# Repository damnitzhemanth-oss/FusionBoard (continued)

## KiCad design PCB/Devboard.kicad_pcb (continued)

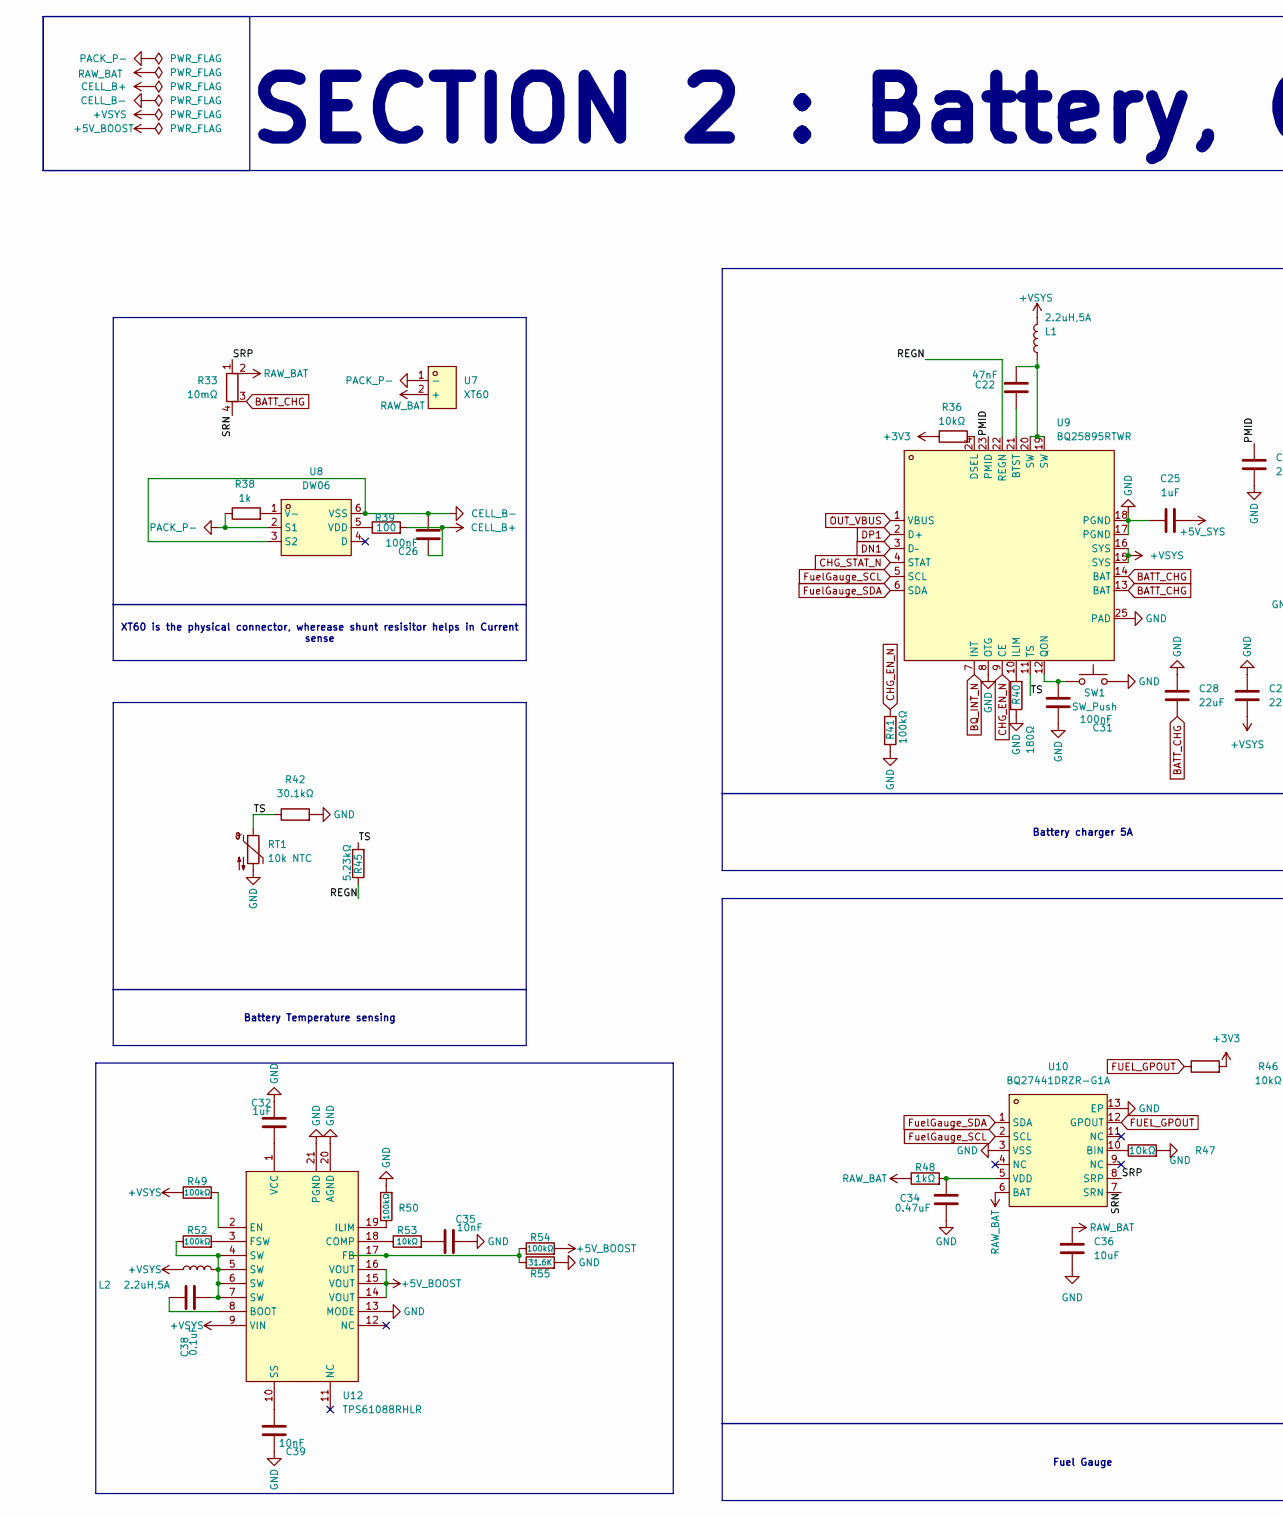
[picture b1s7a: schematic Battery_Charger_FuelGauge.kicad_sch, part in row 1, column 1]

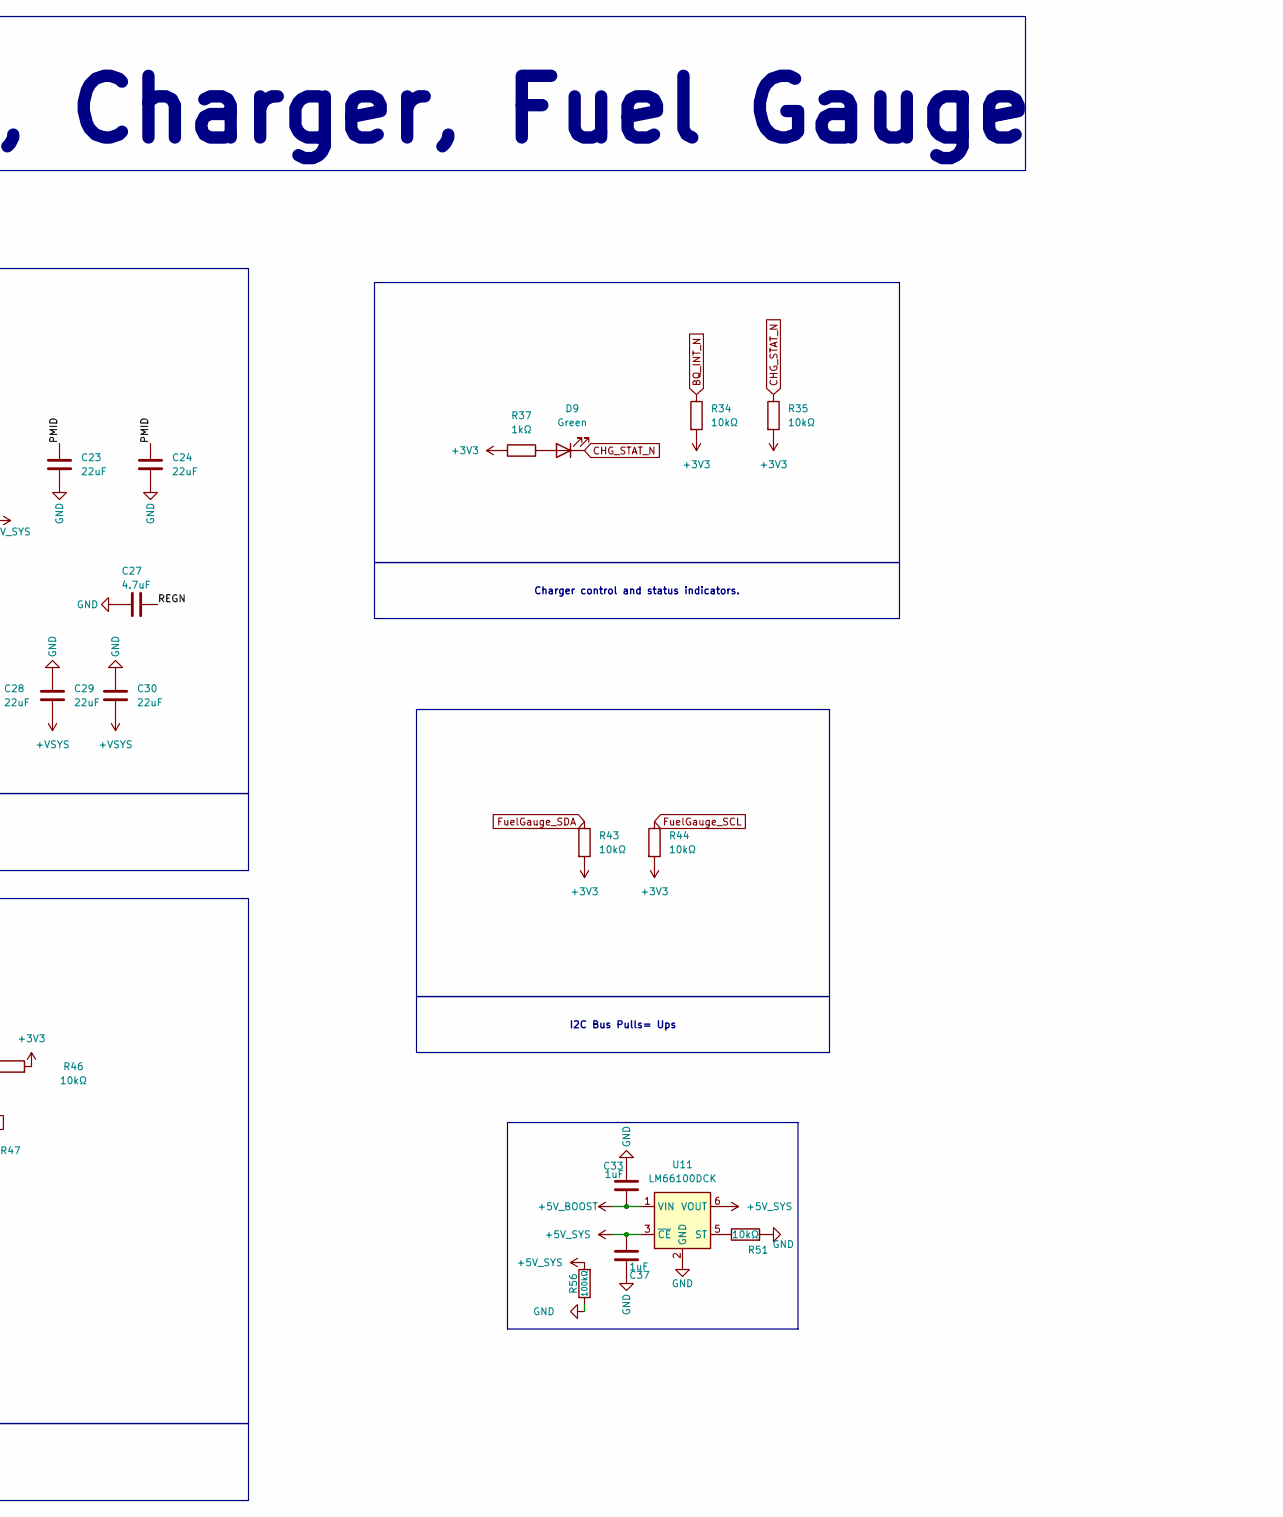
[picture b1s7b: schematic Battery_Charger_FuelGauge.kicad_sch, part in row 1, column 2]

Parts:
C22: 47nF; C_0402_1005Metric
C23, C24, C28, C29, C30: 22uF; C_0805_2012Metric
C25: 1uF; C_0402_1005Metric
C26, C31: 100nF; C_0402_1005Metric
C27: 4.7uF; C_0603_1608Metric
C32, C33, C37: 1uF; C_0805_2012Metric
C34: 0.47uF; C_0402_1005Metric
C35, C39: 10nF; C_0805_2012Metric
C36: 10uF; C_0402_1005Metric
C38: 0.1uF; C_0805_2012Metric
D9: Green; LED_0603_1608Metric
L1, L2: 2.2uH,5A; L_Bourns_SRP1245A
R33: 10mΩ; R_Shunt_Isabellenhuette_BVR4026
R34, R35, R36, R43, R44, R46, R47, R51, R53: 10kΩ; R_0402_1005Metric
R37, R48: 1kΩ; R_0402_1005Metric
R38: 1k; R_0402_1005Metric
R39: 100; R_0402_1005Metric
R40: 180Ω; R_0402_1005Metric
R41, R49, R50, R52, R54, R56: 100kΩ; R_0402_1005Metric
R42: 30.1kΩ; R_0402_1005Metric
R45: 5.23kΩ; R_0402_1005Metric
R55: 31.6K; R_0402_1005Metric
RT1: 10k NTC; R_0603_1608Metric
SW1: SW_Push; SW_SPST_Omron_B3FS-100xP
U7: XT60; CONN-TH_XT60; MPN XT60-M.; LCSC Part C98733
U8: DW06; SOT-23-6_L2.9-W1.6-P0.95-LS2.8-BL; MPN DW06; LCSC Part C917080
U9: BQ25895RTWR; QFN-24_L4.0-W4.0-P0.50-TL-EP2.7; MPN BQ25895RTWR; LCSC Part C80200
U10: BQ27441DRZR-G1A; SON-12_L4.0-W2.5-P0.40-BL-EP; MPN BQ27441DRZR-G1A; LCSC Part C473397
U11: LM66100DCK; SOT-363_SC-70-6
U12: TPS61088RHLR; VQFN-20_L4.6-W3.6-P0.50-BL; MPN TPS61088RHLR; LCSC Part C87357

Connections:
+3V3: R34.2, R35.2, R36.1, R37.1, R43.2, R44.2, R46.2; also elsewhere on the board
+5V_BOOST: C33.2, R54.2, U11.1 (VIN), U12.14 (VOUT), U12.15 (VOUT), U12.16 (VOUT)
+5V_SYS: C25.2, C37.2, R56.2, U11.3 (~CE), U11.6 (VOUT); also elsewhere on the board
+VSYS: C29.1, C30.1, L1.2, L2.1, R49.1, U9.15 (SYS), U9.16 (SYS), U12.9 (VIN)
/Battery.Charger,Fuel Gauge/PMID: C23.2, C24.2, U9.23 (PMID)
/Battery.Charger,Fuel Gauge/REGN: C27.1, R45.1, U9.22 (REGN)
/Battery.Charger,Fuel Gauge/SRN: R33.4, U10.7 (SRN)
/Battery.Charger,Fuel Gauge/SRP: R33.1, U10.8 (SRP)
/Battery.Charger,Fuel Gauge/TS: R42.1, R45.2, RT1.1, U9.11 (TS)
BATT_CHG: C28.1, R33.3, U9.13 (BAT), U9.14 (BAT)
BQ_INT_N: R34.1, U9.7 (INT)
CELL_B+: C26.1, R39.2
CELL_B-: C26.2, U8.3 (S2), U8.6 (VSS)
CHG_EN_N: R41.2, U9.9 (CE)
CHG_STAT_N: D9.1 (K), R35.1, U9.4 (STAT)
DN1: U9.3 (D–); also elsewhere on the board
DP1: U9.2 (D+); also elsewhere on the board
FUEL_GPOUT: R46.1, U10.12 (GPOUT)
FuelGauge_SCL: R44.1, U9.5 (SCL), U10.2 (SCL)
FuelGauge_SDA: R43.1, U9.6 (SDA), U10.1 (SDA)
GND: C23.1, C24.1, C25.1, C27.2, C28.2, C29.2, C30.2, C31.1, C32.1, C33.1, C34.1, C35.1, C36.1, C37.1, C39.1, R40.1, R41.1, R42.2, R47.2, R50.2, R51.2, R55.2, R56.1, RT1.2, SW1.2, U9.8 (OTG), U9.17 (PGND), U9.18 (PGND), U9.25 (PAD), U10.3 (VSS), U10.13 (EP), U11.2 (GND), U12.13 (MODE), U12.20 (AGND), U12.21 (PGND); also elsewhere on the board
unnamed: C22.2, L1.1, U9.19 (SW), U9.20 (SW)
unnamed: C35.2, R53.2
unnamed: C38.1, L2.2, R52.1, U12.4 (SW), U12.5 (SW), U12.6 (SW), U12.7 (SW)
unnamed: D9.2 (A), R37.2
unnamed: R38.2, U8.1 (V-)
unnamed: R39.1, U8.5 (VDD)
unnamed: C22.1, U9.21 (BTST)
unnamed: R36.2, U9.24 (DSEL)
unnamed: R40.2, U9.10 (ILIM)
unnamed: C31.2, SW1.1, U9.12 (QON)
unnamed: R47.1, U10.10 (BIN)
unnamed: C34.2, R48.2, U10.5 (VDD)
unnamed: R51.1, U11.5 (ST)
unnamed: C38.2, U12.8 (BOOT)
unnamed: R53.1, U12.18 (COMP)
unnamed: R49.2, U12.2 (EN)
unnamed: R54.1, R55.1, U12.17 (FB)
unnamed: R52.2, U12.3 (FSW)
unnamed: R50.1, U12.19 (ILIM)
unnamed: C39.2, U12.10 (SS)
unnamed: C32.2, U12.1 (VCC)
OUT_VBUS: U9.1 (VBUS); also elsewhere on the board
PACK_P-: R38.1, U7.1 (-), U8.2 (S1)
RAW_BAT: C36.2, R33.2, R48.1, U7.2 (+), U10.6 (BAT); also elsewhere on the board

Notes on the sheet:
SECTION 2 : Battery, Charger, Fuel Gauge
I2C Bus Pulls= Ups
Charger control and status indicators.
Battery Temperature sensing
Fuel Gauge
XT60 is the physical connector, wherease shunt resisitor helps in Current sense
Battery charger 5A

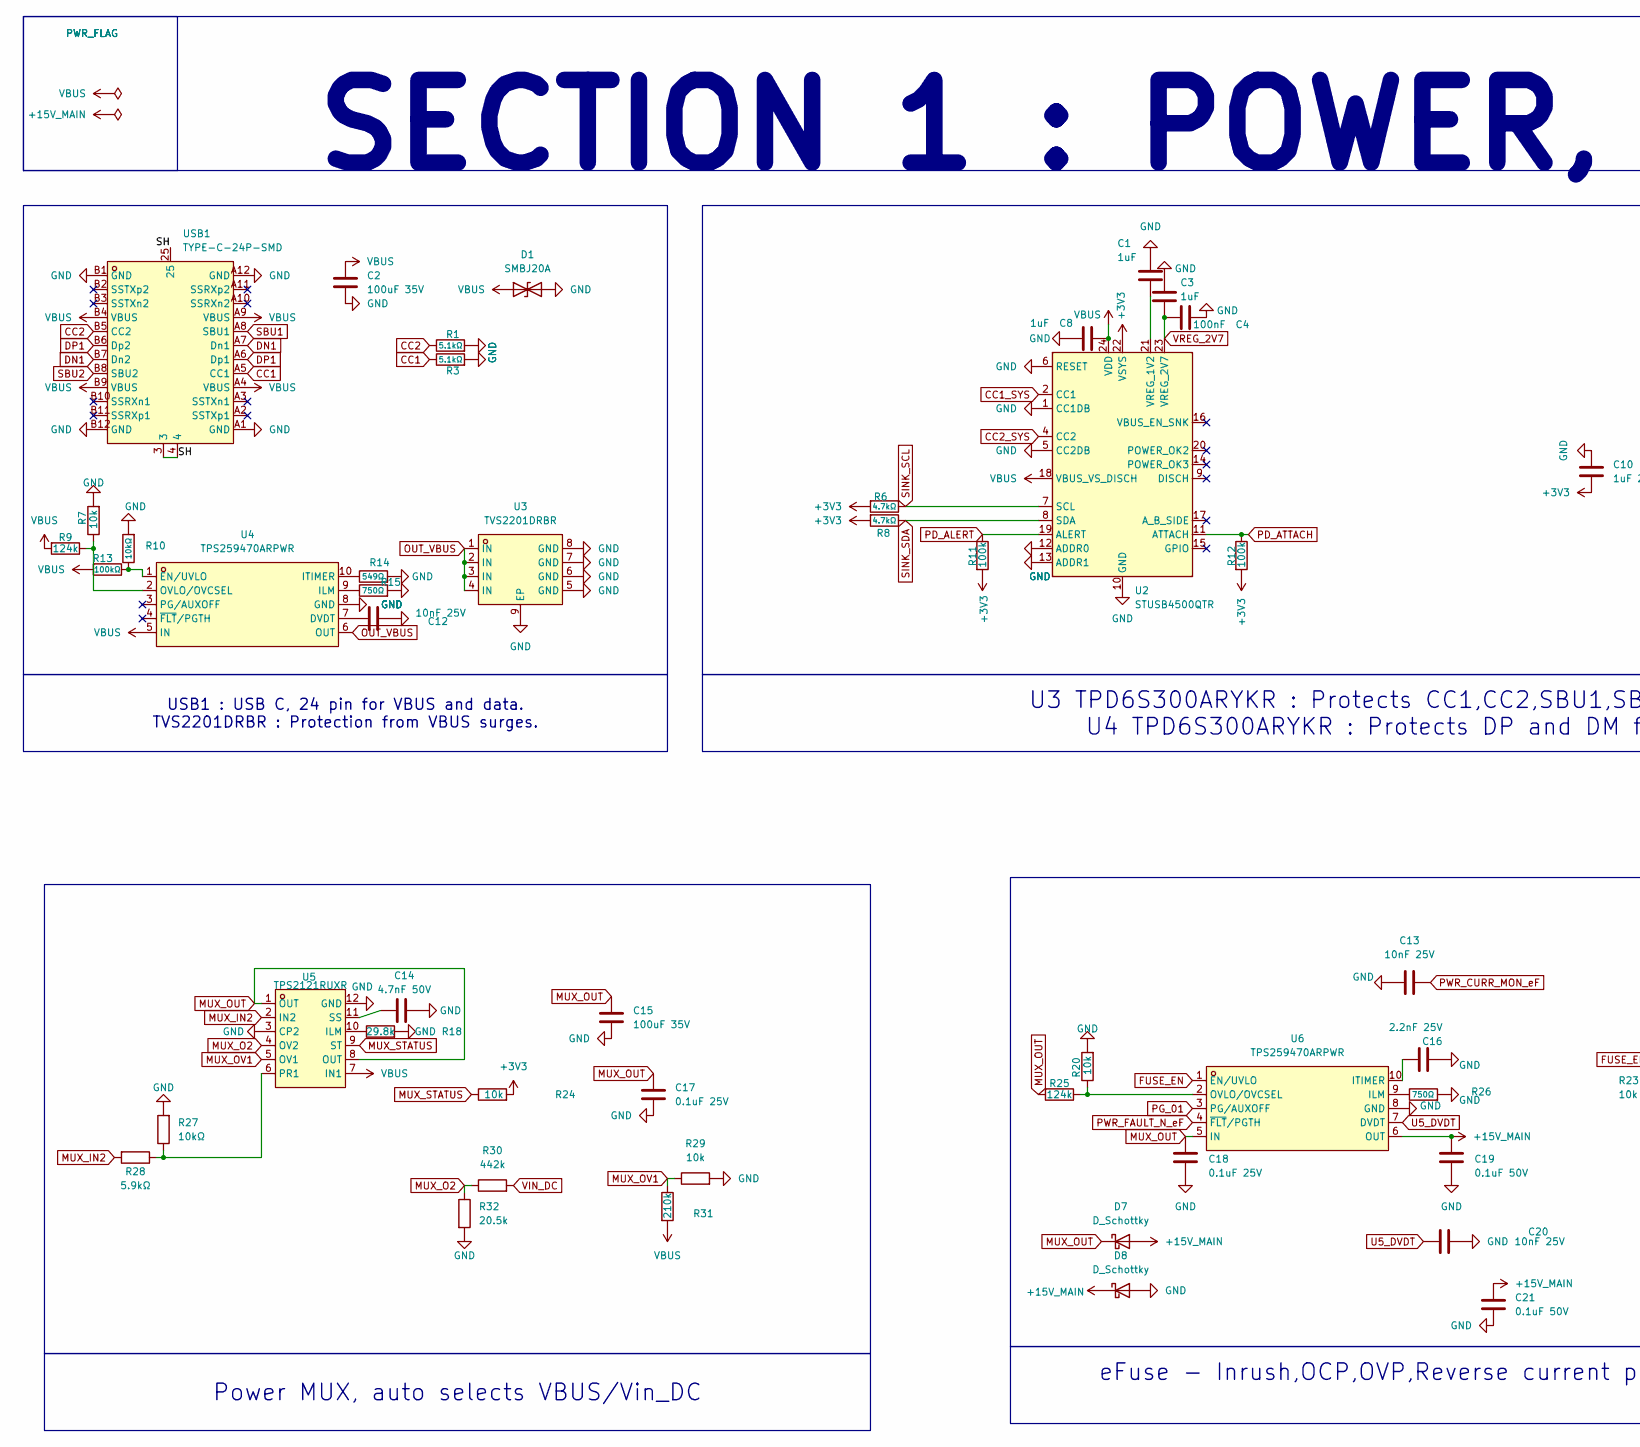
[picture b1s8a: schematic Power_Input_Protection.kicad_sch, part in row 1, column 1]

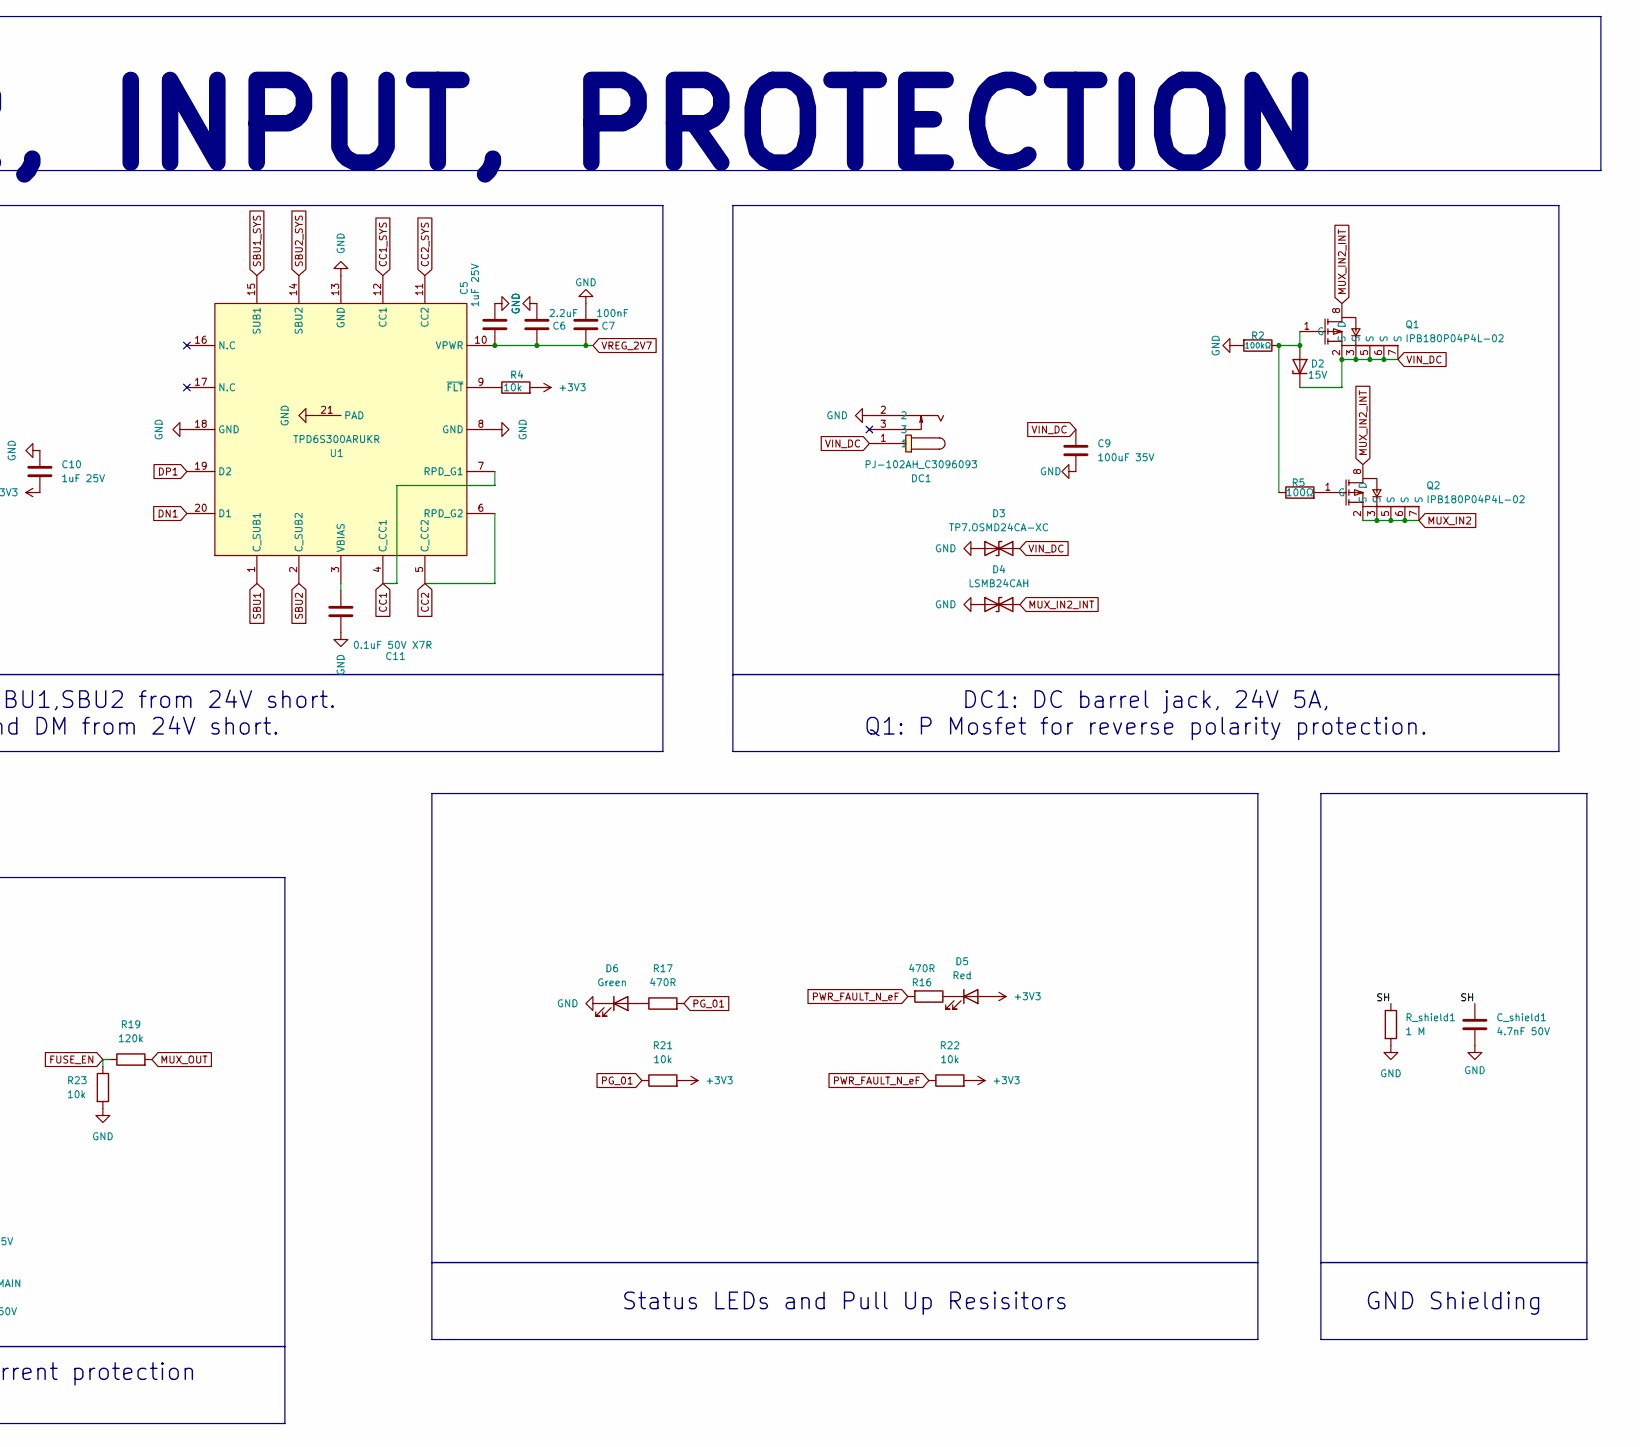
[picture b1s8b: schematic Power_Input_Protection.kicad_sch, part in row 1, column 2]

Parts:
C1, C3: 1uF; C_0402_1005Metric
C2: 100uF 35V; C_0402_1005Metric
C4, C7: 100nF; C_0402_1005Metric
C5, C10: 1uF 25V; C_0402_1005Metric
C6: 2.2uF; C_0402_1005Metric
C8: 1uF; C_1210_3225Metric
C9, C15: 100uF 35V; C_1210_3225Metric
C11: 0.1uF 50V X7R; C_0402_1005Metric
C12, C13, C20: 10nF 25V; C_0402_1005Metric
C14: 4.7nF 50V; C_0402_1005Metric
C16: 2.2nF 25V; C_0402_1005Metric
C17, C18: 0.1uF 25V; C_0402_1005Metric
C19, C21: 0.1uF 50V; C_0402_1005Metric
C_shield1: 4.7nF 50V; C_0402_1005Metric
D1: SMBJ20A; D_SMC
D2: 15V; D_SMC
D3: TP7.OSMD24CA-XC; D_SMC
D4: LSMB24CAH; D_SMC
D5: Red; LED_0603_1608Metric
D6: Green; LED_0603_1608Metric
D7, D8: D_Schottky; D_SMC
DC1: PJ-102AH_C3096093; DC-IN-TH_PJ-102AH; MPN PJ-102AH; LCSC Part C3096093
Q1, Q2: IPB180P04P4L-02; TO-263-7_TabPin8; MPN IPB180P04P4L-02(TOKMAS); LCSC Part C21547650
R1, R3: 5.1kΩ; R_0402_1005Metric
R2, R13: 100kΩ; R_0402_1005Metric
R4, R7, R20, R21, R22, R23, R24, R29: 10k; R_0402_1005Metric
R5: 100Ω; R_0402_1005Metric
R6, R8: 4.7kΩ; R_0402_1005Metric
R9, R25: 124k; R_0402_1005Metric
R10, R27: 10kΩ; R_0402_1005Metric
R11, R12: 100k; R_0402_1005Metric
R14: 549Ω; R_0402_1005Metric
R15, R26: 750Ω; R_0402_1005Metric
R16, R17: 470R; R_0402_1005Metric
R18: 29.8k; R_0402_1005Metric
R19: 120k; R_0402_1005Metric
R28: 5.9kΩ; R_0402_1005Metric
R30: 442k; R_0402_1005Metric
R31: 210k; R_0402_1005Metric
R32: 20.5k; R_0402_1005Metric
R_shield1: 1 M; R_0402_1005Metric
U1: TPD6S300ARUKR; WQFN-20_L3.0-W3.0-P0.40-TL-EP1.7; MPN TPD6S300ARUKR; LCSC Part C2876380
U2: STUSB4500QTR; QFN-24-1EP_4x4mm_P0.5mm_EP2.7x2.7mm
U3: TVS2201DRBR; VSON-8_L3.0-W3.0-P0.65-BL-EP; MPN TVS2201DRBR; LCSC Part C1849889
U4, U6: TPS259470ARPWR; VQFN-10_L2.0-W2.0-P0.45-TL; MPN TPS259470ARPWR; LCSC Part C3662799
U5: TPS2121RUXR; VQFN-HR-12_L2.5-W2.0-P0.50-BL; MPN TPS2121RUXR; LCSC Part C485916
USB1: TYPE-C-24P-SMD; USB-C-SMD_TYPE-C-24P-SMD; MPN TYPE-C-24P-SMD; LCSC Part C53207146

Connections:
+3V3: C10.2, D5.2 (A), R4.2, R6.2, R8.2, R11.2, R12.2, R21.2, R22.2, R24.2, U2.22 (VSYS); also elsewhere on the board
+15V_MAIN: C19.1, C21.1, D7.2 (A), D8.1 (K), U6.6 (OUT); also elsewhere on the board
/Power,Input,Protection/SH: C_shield1.1, R_shield1.1, USB1.3, USB1.4, USB1.25
CC1: R3.1, U1.4 (C_CC1), U1.7 (RPD_G1), USB1.A5 (CC1)
CC1_SYS: U1.12 (CC1), U2.2 (CC1)
CC2: R1.1, U1.5 (C_CC2), U1.6 (RPD_G2), USB1.B5 (CC2)
CC2_SYS: U1.11 (CC2), U2.4 (CC2)
DN1: U1.20 (D1), USB1.A7 (Dn1), USB1.B7 (Dn2); also elsewhere on the board
DP1: U1.19 (D2), USB1.A6 (Dp1), USB1.B6 (Dp2); also elsewhere on the board
FUSE_EN: R19.1, R23.1, U6.1 (EN/UVLO)
GND: C1.2, C2.2, C3.2, C4.1, C5.1, C6.1, C7.1, C8.2, C9.2, C10.1, C11.1, C12.2, C13.1, C14.2, C15.2, C16.2, C17.2, C18.2, C19.2, C20.2, C21.2, C_shield1.2, D1.2 (A2), D3.1 (A1), D4.1 (A1), D6.1 (K), D8.2 (A), DC1.2, R1.2, R2.2, R3.2, R7.2, R10.2, R14.2, R15.2, R18.2, R20.2, R23.2, R26.2, R27.2, R29.2, R32.2, R_shield1.2, U1.8 (GND), U1.13 (GND), U1.18 (GND), U1.21 (PAD), U2.1 (CC1DB), U2.5 (CC2DB), U2.6 (RESET), U2.10 (GND), U2.12 (ADDR0), U2.13 (ADDR1), U2.25 (GND), U3.5 (GND), U3.6 (GND), U3.7 (GND), U3.8 (GND), U3.9 (EP), U4.8 (GND), U5.3 (CP2), U5.12 (GND), U6.8 (GND), USB1.A1 (GND), USB1.A12 (GND), USB1.B1 (GND), USB1.B12 (GND); also elsewhere on the board
MUX_IN2: Q2.2 (S), Q2.3 (S), Q2.5 (S), Q2.6 (S), Q2.7 (S), R28.2, U5.2 (IN2)
MUX_IN2_INT: D4.2 (A2), Q1.8 (D), Q2.8 (D)
MUX_O2: R30.1, R32.1, U5.4 (OV2)
MUX_OUT: C15.1, C17.1, C18.1, D7.1 (K), R19.2, R25.2, U5.1 (OUT), U5.8 (OUT), U6.5 (IN)
MUX_OV1: R29.1, R31.1, U5.5 (OV1)
MUX_STATUS: R24.1, U5.9 (ST)
unnamed: D2.2 (A), Q1.1 (G), R2.1, R5.1
unnamed: D5.1 (K), R16.1
unnamed: D6.2 (A), R17.1
unnamed: Q2.1 (G), R5.2
unnamed: C11.2, U1.3 (VBIAS)
unnamed: R4.1, U1.9 (~FLT)
unnamed: C1.1, U2.21 (VREG_1V2)
unnamed: C12.1, U4.7 (DVDT)
unnamed: R10.1, R13.1, U4.1 (EN/UVLO)
unnamed: R15.1, U4.9 (ILM)
unnamed: R14.1, U4.10 (ITIMER)
unnamed: R7.1, R9.1, U4.2 (OVLO/OVCSEL)
unnamed: R18.1, U5.10 (ILM)
unnamed: R27.1, R28.1, U5.6 (PR1)
unnamed: C14.1, U5.11 (SS)
unnamed: R26.1, U6.9 (ILM)
unnamed: C16.1, U6.10 (ITIMER)
unnamed: R20.1, R25.1, U6.2 (OVLO/OVCSEL)
OUT_VBUS: U3.1 (IN), U3.2 (IN), U3.3 (IN), U3.4 (IN), U4.6 (OUT); also elsewhere on the board
PD_ALERT: R11.1, U2.19 (ALERT)
PD_ATTACH: R12.1, U2.11 (ATTACH)
PG_01: R17.2, R21.1, U6.3 (PG/AUXOFF)
PWR_CURR_MON_eF: C13.2
PWR_FAULT_N_eF: R16.2, R22.1, U6.4 (~FLT/PGTH)
SBU1: U1.1 (C_SUB1), USB1.A8 (SBU1)
SBU1_SYS: U1.15 (SUB1)
SBU2: U1.2 (C_SUB2), USB1.B8 (SBU2)
SBU2_SYS: U1.14 (SBU2)
SINK_SCL: R6.1, U2.7 (SCL)
SINK_SDA: R8.1, U2.8 (SDA)
U5_DVDT: C20.1, U6.7 (DVDT)
VBUS: C2.1, C8.1, D1.1 (A1), R9.2, R13.2, R31.2, U2.18 (VBUS_VS_DISCH), U2.24 (VDD), U4.5 (IN), U5.7 (IN1), USB1.A4 (VBUS), USB1.A9 (VBUS), USB1.B4 (VBUS), USB1.B9 (VBUS); also elsewhere on the board
VIN_DC: C9.1, D2.1 (K), D3.2 (A2), DC1.1, Q1.2 (S), Q1.3 (S), Q1.5 (S), Q1.6 (S), Q1.7 (S), R30.2
VREG_2V7: C3.1, C4.2, C5.2, C6.2, C7.2, U1.10 (VPWR), U2.23 (VREG_2V7)

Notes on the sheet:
SECTION 1 : POWER, INPUT, PROTECTION
USB1 : USB C, 24 pin for VBUS and data. TVS2201DRBR : Protection from VBUS surges.
eFuse - Inrush,OCP,OVP,Reverse current protection
DC1: DC barrel jack, 24V 5A, Q1: P Mosfet for reverse polarity protection.
Power MUX, auto selects VBUS/Vin_DC
Status LEDs and Pull Up Resisitors
U3 TPD6S300ARYKR : Protects CC1,CC2,SBU1,SBU2 from 24V short. U4 TPD6S300ARYKR : Protects DP and DM from 24V short.
GND Shielding

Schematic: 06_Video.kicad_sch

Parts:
C448, C449, C450, C452: 100nF; C_0402_1005Metric
C451, C453: 10uF; C_0402_1005Metric
J13: Conn_01x22; Hirose_FH12-22S-0.5SH_1x22-1MP_P0.50mm_Horizontal
R177, R178: 4.7kΩ; R_0402_1005Metric
R179, R180: 10kΩ; R_0402_1005Metric

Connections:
+3V3: C450.1, C451.2, C452.1, C453.2, J13.21, J13.22, R177.2, R178.2, R179.2; also elsewhere on the board
CAM_PWDN: J13.20, R180.1; also elsewhere on the board
CAM_RST_N: J13.19, R179.1; also elsewhere on the board
GND: C448.2, C449.2, C450.2, C451.1, C452.2, C453.1, J13.1, J13.4, J13.7, J13.10, J13.13, J13.16, R180.2; also elsewhere on the board
I2C_SCL_4: J13.17, R177.1; also elsewhere on the board
I2C_SDA_4: J13.18, R178.1; also elsewhere on the board
MIPI_CLK_N: C449.1, J13.8; also elsewhere on the board
MIPI_CLK_P: C448.1, J13.9; also elsewhere on the board
MIPI_D0_N: J13.2; also elsewhere on the board
MIPI_D0_P: J13.3; also elsewhere on the board
MIPI_D1_N: J13.5; also elsewhere on the board
MIPI_D1_P: J13.6; also elsewhere on the board
MIPI_D2_N: J13.11; also elsewhere on the board
MIPI_D2_P: J13.12; also elsewhere on the board
MIPI_D3_N: J13.14; also elsewhere on the board
MIPI_D3_P: J13.15; also elsewhere on the board

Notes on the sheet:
SECTION 6 : Video

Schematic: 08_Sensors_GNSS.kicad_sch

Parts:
C501, C502, C503, C505, C506, C508, C509, C510, C511: 0.1uF; C_0402_1005Metric
C507: 10uF; C_0402_1005Metric
R196, R197, R201, R202, R203, R204, R205, R206: 5kΩ; R_0402_1005Metric
U50: TMP117DRVR; WSON-6-1EP_2x2mm_P0.65mm_EP1x1.6mm
U51: ICM-42688-P; LGA14_2P5X3X0P91_TDK-L
U52: MMC5983MA; LGA-16_L3.0-W3.0-P0.50-BL_SQ; MPN MMC5983MA; LCSC Part C404329
U54: BMP581; LGA-10_L2.0-W2.0-P0.50-TL_BMP581; MPN BMP581; LCSC Part C5362283
U55: MAX-M10S-00B; SMD-18_L10.1-W9.7-P1.10-TL_SKG09F; MPN MAX-M10S-00B; LCSC Part C4153167

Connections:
+3V3: C501.2, C502.1, C503.2, C505.1, C506.2, C508.1, C509.2, C510.1, C511.2, R196.1, R197.2, R201.2, R202.2, R203.2, R204.2, R205.2, R206.2, U50.5 (V+), U51.5 (VDDIO), U51.8 (VDD), U51.12 (AP_CS), U52.2 (VDD), U52.4 (SPI_CS), U52.13 (VDDIO), U54.1 (VDDIO), U54.6 (CSB), U54.10 (VDD), U55.5 (EXTINT), U55.6 (V_BCKP), U55.7 (V_IO), U55.8 (VCC), U55.9 (RESET_N), U55.14 (VCC_RF), U55.15 (VIO_SEL), U55.18 (SAFEBOOT_N); also elsewhere on the board
GND: C501.1, C502.2, C503.1, C505.2, C506.1, C507.1, C508.2, C509.1, C510.2, C511.1, U50.2 (GND), U50.4 (ADD0), U51.1 (AP_SDO/AP_AD0), U51.6 (GND), U52.9 (GND), U52.11 (GND), U54.3 (VSS), U54.5 (SDO), U54.8 (VSS), U54.9 (VSS), U55.1 (GND), U55.10 (GND), U55.12 (GND); also elsewhere on the board
GNSS_PPS: U55.4 (TIMEPULSE); also elsewhere on the board
I2C_SCL1_0: R205.1, U55.17 (SCL); also elsewhere on the board
I2C_SCL_0: U51.13 (AP_SCL/AP_SCLK); also elsewhere on the board
I2C_SCL_3: R197.1, U50.1 (SCL); also elsewhere on the board
I2C_SCL_6: R201.1, U52.1 (SCL/SPI_SCK); also elsewhere on the board
I2C_SCL_7: R203.1, U54.2 (SCK); also elsewhere on the board
I2C_SDA1_0: R206.1, U55.16 (SDA); also elsewhere on the board
I2C_SDA_0: U51.14 (AP_SDA/AP_SDIO/AP_SDI); also elsewhere on the board
I2C_SDA_3: R196.2, U50.6 (SDA); also elsewhere on the board
I2C_SDA_6: R202.1, U52.16 (SDA/SPI_SDI); also elsewhere on the board
I2C_SDA_7: R204.1, U54.4 (SDI); also elsewhere on the board
unnamed: C507.2, U52.10 (CAP)
UART1_RX: U55.3 (RXD); also elsewhere on the board
UART1_TX: U55.2 (TXD); also elsewhere on the board

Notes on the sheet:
SECTION 8 : Sensors
IMU (Gyro Scope)
Magnetometer
GNSS
Temp Sensor
Barometer

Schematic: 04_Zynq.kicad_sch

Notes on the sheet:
Zynq: Master Page

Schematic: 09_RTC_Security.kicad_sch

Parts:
BT1: Battery_Cell; BatteryHolder_Keystone_1057_1x2032
C512, C513, C514, C515, C516: 0.1uF; C_0402_1005Metric
D10: RB521S30; D_0201_0603Metric
R207: 10kΩ; R_0402_1005Metric
U56: ATECC608B-MAHDA; DFN-8-1EP_3x2mm_P0.5mm_EP1.3x1.5mm
U57: OPTIGA TPM SLB 9673 FW26; QFN50P500X500X60-33N-V2

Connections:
+3V3: C513.1, C515.2, C516.1, D10.1 (K), R207.1, U56.8 (VCC), U57.1 (VDD_1), U57.22 (VDD_3); also elsewhere on the board
GND: BT1.2 (-), C512.2, C513.2, C514.1, C515.1, C516.2, U56.4 (GND), U56.9 (EP), U57.2 (GND_1), U57.9 (GND_2), U57.14 (VDD_2), U57.23 (GND_3), U57.32 (GND_4), U57.33 (EP); also elsewhere on the board
I2C_SCL1_1: U56.6 (SCL); also elsewhere on the board
I2C_SCL1_2: U57.30 (SCL); also elsewhere on the board
I2C_SDA1_1: U56.5 (SDA); also elsewhere on the board
I2C_SDA1_2: U57.29 (SDA); also elsewhere on the board
unnamed: C512.1, C514.2
unnamed: R207.2, U57.17 (RST_N)
VBAT_RTC: BT1.1 (+), D10.2 (A)

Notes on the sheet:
Coin Cell
TPM
Secure Element
SECTION 9 : RTC

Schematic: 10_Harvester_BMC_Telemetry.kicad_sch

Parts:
C517, C519, C520, C521, C522, C523: 0.1uF; C_0402_1005Metric
C518: 22F 5.5V; C_Radial_D16.0mm_H31.5mm_P7.50mm
D11, D12: RB521S30; D_0201_0603Metric
J2: Conn_01x03_Pin; PinHeader_1x03_P2.00mm_Vertical
J4, J5: Conn_01x02_Pin; PinSocket_1x02_P2.00mm_Vertical
L13, L14: 220 nH; L_0603_1608Metric
R208: 4.02MΩ; R_0402_1005Metric
R209, R210: 1MΩ; R_0402_1005Metric
R211: 3MΩ; R_0402_1005Metric
R212: 10kΩ; R_0402_1005Metric
U58: BQ25570; QFN-20-1EP_3.5x3.5mm_P0.5mm_EP2x2mm
U59: STM32G0B1RBT6; LQFP-64_10x10mm_P0.5mm

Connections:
+3V3: D11.2 (A); also elsewhere on the board
+3V3_BMC: C519.1, C522.1, C523.2, D11.1 (K), D12.1 (K), J2.2, J5.2, U59.6 (VBAT), U59.7 (VREF+), U59.8 (VDD); also elsewhere on the board
+3V3_HARVEST: D12.2 (A), L14.2, U58.14 (VOUT)
/Harvester, BMC, Telemetry/HARVEST_IN: R208.1, U58.2 (VIN_DC)
/Harvester, BMC, Telemetry/SUPERCAP_P: C517.2, C518.1, L13.1, R211.1, R212.1, U58.6 (VOUT_EN), U58.18 (VBAT)
EPD_BUSY: U59.29 (PB2); also elsewhere on the board
EPD_CS: U59.21 (PA4); also elsewhere on the board
EPD_DC: U59.27 (PB0); also elsewhere on the board
EPD_MISO: U59.23 (PA6); also elsewhere on the board
EPD_MOSI: U59.24 (PA7); also elsewhere on the board
EPD_RST: U59.28 (PB1); also elsewhere on the board
EPD_SCK: U59.22 (PA5); also elsewhere on the board
GND: C517.1, C518.2, C519.2, C520.2, C521.1, C522.2, C523.1, J2.3, J5.1, R209.1, R210.1, U58.1 (VSS), U58.8 (VRDIV), U58.9 (VSS), U58.15 (VSS), U58.17 (VSS), U58.21 (VSS), U59.9 (VSS); also elsewhere on the board
I2C_BMC_SCL: U59.30 (PB10)
I2C_BMC_SDA: U59.31 (PB11)
I2C_SCL1_3: U59.60 (PB6); also elsewhere on the board
I2C_SDA1_3: U59.61 (PB7); also elsewhere on the board
unnamed: C520.1, C521.2
unnamed: J2.1, U59.12 (PF2)
unnamed: J4.1, U59.46 (PA14)
unnamed: J4.2, U59.45 (PA13)
unnamed: L13.2, U58.20 (LBOOST)
unnamed: L14.1, U58.16 (LBUCK)
unnamed: R210.2, R211.2, U58.7 (VBAT_OV)
unnamed: R208.2, R209.2, U58.3 (VOC_SAMP)
unnamed: R212.2, U58.5 (~EN)

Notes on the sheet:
Energy Harvester
SECTION 10 : Harvester, BMC, Telemetry
Always On MCU

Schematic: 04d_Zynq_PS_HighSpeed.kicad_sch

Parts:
C412, C413, C414, C415, C416, C417, C418, C419, C420, C421, C423, C425, C426, C427, C428, C430: 100nF; C_0402_1005Metric
C422: 1nF; C_0402_1005Metric
C424, C429, C431: 10uF; C_0805_2012Metric
CN1: 1-2199230-6; PCIE-SMD_1-2199230-6; MPN 1-2199230-6; LCSC Part C4710843
FB10: 120Ω@100MHz; L_01005_0402Metric
J12: SFP+; Connector_SFP_and_Cage
L11: DLW21HN900SQ2L-CUTTAPE; FILTER-SMD_4P-L2.0-W1.3-BL_DLW21; MPN DLW21HN900SQ2L; LCSC Part C80529
R163, R164: 5.1kΩ; R_0402_1005Metric
R165, R166: 100kΩ; R_0402_1005Metric
R167: 1MΩ; R_0402_1005Metric
R168, R175: 50Ω; R_0402_1005Metric
R169, R171: 33Ω; R_0402_1005Metric
R170, R172, R173, R174, R194: 10kΩ; R_0402_1005Metric
U39: TPD4E05U06DQA; USON-10_2.5x1.0mm_P0.5mm
U40: TXS0102DQE; X2SON-8_1.4x1mm_P0.35mm
USB3: TYPE-C-24P-SMD; USB-C-SMD_TYPE-C-24P-SMD; MPN TYPE-C-24P-SMD; LCSC Part C53207146
USB4: 472720001; CONN-SMD_472720001; MPN 472720001; LCSC Part C587824
Y4: SiT9365AI-4B2-33E100.0000000; Oscillator_SMD_SiTime_PQFD-6L_3.2x2.5mm

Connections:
+3V3: C423.2, C424.2, C426.2, C430.2, C431.2, CN1.2, CN1.4, CN1.12, CN1.14, CN1.16, CN1.18, CN1.70, CN1.72, CN1.74, FB10.2, R170.1, R172.1, R173.1, R174.1, R194.1, U40.1 (VCCA), U40.8 (VCCB), USB4.20, Y4.6 (VDD); also elsewhere on the board
/Zynq Section/High Speed Peripherals/CC1: R163.1, USB3.A5 (CC1)
/Zynq Section/High Speed Peripherals/CC2: R164.1, USB3.B5 (CC2)
/Zynq Section/High Speed Peripherals/CLKREQ#: CN1.52, R173.2, U40.3 (A2)
/Zynq Section/High Speed Peripherals/D1+: L11.4, U39.1 (D1+), USB3.A2 (SSTXp1), USB3.B2 (SSTXp2)
/Zynq Section/High Speed Peripherals/D1-: L11.3, U39.4 (D2+), USB3.A3 (SSTXn1), USB3.B3 (SSTXn2)
/Zynq Section/High Speed Peripherals/PERST#: CN1.50, R174.2, U40.2 (A1)
/Zynq Section/High Speed Peripherals/PEWAKE#: CN1.54, R172.2
/Zynq Section/High Speed Peripherals/REFCLK_N_TERM: C427.1, CN1.53
/Zynq Section/High Speed Peripherals/REFCLK_P_TERM: C425.1, CN1.55
/Zynq Section/High Speed Peripherals/SH: C422.2, R167.1, USB3.3, USB3.4, USB3.25
DP_AUX_N: USB4.17; also elsewhere on the board
DP_AUX_P: USB4.15; also elsewhere on the board
DP_HPD: USB4.18
DP_TX0_N: C416.1; also elsewhere on the board
DP_TX0_P: C412.1; also elsewhere on the board
GND: C420.2, C421.2, C422.1, C423.1, C424.1, C426.1, C428.1, C429.1, C430.1, C431.1, CN1.1, CN1.3, CN1.9, CN1.15, CN1.21, CN1.27, CN1.33, CN1.39, CN1.45, CN1.51, CN1.57, CN1.71, CN1.73, CN1.75, J12.1 (VeeT), J12.10 (VeeR), J12.11 (VeeR), J12.14 (VeeR), J12.17 (VeeT), J12.20 (VeeT), J12.CAGE, R163.2, R164.2, R165.2, R167.2, R168.2, R175.2, U39.3 (GND), U39.8 (GND), U40.4 (GND), USB3.A1 (GND), USB3.A12 (GND), USB3.B1 (GND), USB3.B12 (GND), USB4.2, USB4.5, USB4.8, USB4.11, USB4.13, USB4.14, USB4.16, USB4.19, USB4.21 (GND), USB4.22 (GND), USB4.23 (GND), USB4.24 (GND), Y4.3 (GND); also elsewhere on the board
I2C_SCL_2_T: J12.5 (SCL); also elsewhere on the board
I2C_SDA_2_T: J12.4 (SDA); also elsewhere on the board
MIO50: U40.7 (B1); also elsewhere on the board
MIO51: U40.6 (B2); also elsewhere on the board
unnamed: C412.2, C413.1
unnamed: C413.2, C414.1
unnamed: C414.2, C415.1
unnamed: C415.2, USB4.1
unnamed: C416.2, C417.1
unnamed: C417.2, C418.1
unnamed: C418.2, C419.1
unnamed: C419.2, USB4.3
unnamed: C425.2, R168.1, R169.2
unnamed: C427.2, R171.2, R175.1
unnamed: C428.2, C429.2, FB10.1, J12.15 (VccR), J12.16 (VccT)
unnamed: R194.2, U40.5 (OE)
unnamed: R170.2, Y4.1 (OE)
unnamed: R169.1, Y4.4 (OUT+)
unnamed: R171.1, Y4.5 (OUT-)
PCIE_RX_N: CN1.29; also elsewhere on the board
PCIE_RX_P: CN1.31; also elsewhere on the board
PCIE_TX_N: CN1.35; also elsewhere on the board
PCIE_TX_P: CN1.37; also elsewhere on the board
SFP_RX_N: J12.12 (RD-); also elsewhere on the board
SFP_RX_P: J12.13 (RD+); also elsewhere on the board
SFP_TX_N: J12.19 (TD-); also elsewhere on the board
SFP_TX_P: J12.18 (TD+); also elsewhere on the board
USB3_RX_N: U39.5 (D2-), USB3.A10 (SSRXn2), USB3.B10 (SSRXn1); also elsewhere on the board
USB3_RX_P: U39.2 (D1-), USB3.A11 (SSRXp2), USB3.B11 (SSRXp1); also elsewhere on the board
USB3_TX_N: C421.1, L11.2; also elsewhere on the board
USB3_TX_P: C420.1, L11.1; also elsewhere on the board
USB3_VBUS: R166.2, USB3.A4 (VBUS), USB3.A9 (VBUS), USB3.B4 (VBUS), USB3.B9 (VBUS); also elsewhere on the board
USB3_VBUS_NET: R165.1, R166.1; also elsewhere on the board
USBDM_DN2: USB3.A7 (Dn1), USB3.B7 (Dn2); also elsewhere on the board
USBDP_DN2: USB3.A6 (Dp1), USB3.B6 (Dp2); also elsewhere on the board

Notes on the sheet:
SECTION 04d : High Speed Peripherals
DisplayPort
USB3 Super Speed
PCIE
SEF CAGE
